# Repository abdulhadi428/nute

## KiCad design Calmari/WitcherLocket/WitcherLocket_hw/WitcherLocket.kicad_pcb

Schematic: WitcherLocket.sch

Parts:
C1, C3: 0.1u
C2, C4: 10u
D1: BAT54WS; SOD323
D2, D3, D4, D5, D6, D7, D8, D9: LED
DA1: NCP1400
HOLE1, HOLE2, HOLE3, HOLE4, HOLE5, HOLE6: HOLE_METALLED
L1: 22uH
R1, R3: 51R; RES_0603
R2, R4: 10R; RES_0603
SW1, SW2, SW3, SW4: SWITCH_2X
XL1, XL2: CONN_1

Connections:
+3.3V: C3.1, C4.1, D1.C, DA1.1 (CE), DA1.2 (OUT), SW1.2, SW2.2, SW3.2, SW4.2
+BATT: SW1.5, SW2.5, SW3.5, SW4.5, XL1.1
/Lout: D1.A, DA1.5 (LX), L1.1
/PWR_IN: C1.1, C2.1, L1.2, SW1.4, SW2.4, SW3.4, SW4.4
GND: C1.2, C2.2, C3.2, C4.2, D2.C, D3.C, D4.C, D5.C, D6.C, D7.C, D8.C, D9.C, DA1.4 (GND), XL2.1
unnamed: R2.1, SW2.3
unnamed: R3.1, SW3.3
unnamed: R4.1, SW4.3
unnamed: R1.1, SW1.3
unnamed: D4.A, D8.A, R3.2
unnamed: D5.A, D9.A, R4.2
unnamed: D2.A, D6.A, R1.2
unnamed: D3.A, D7.A, R2.2

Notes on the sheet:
-BATTERY
+BATTERY

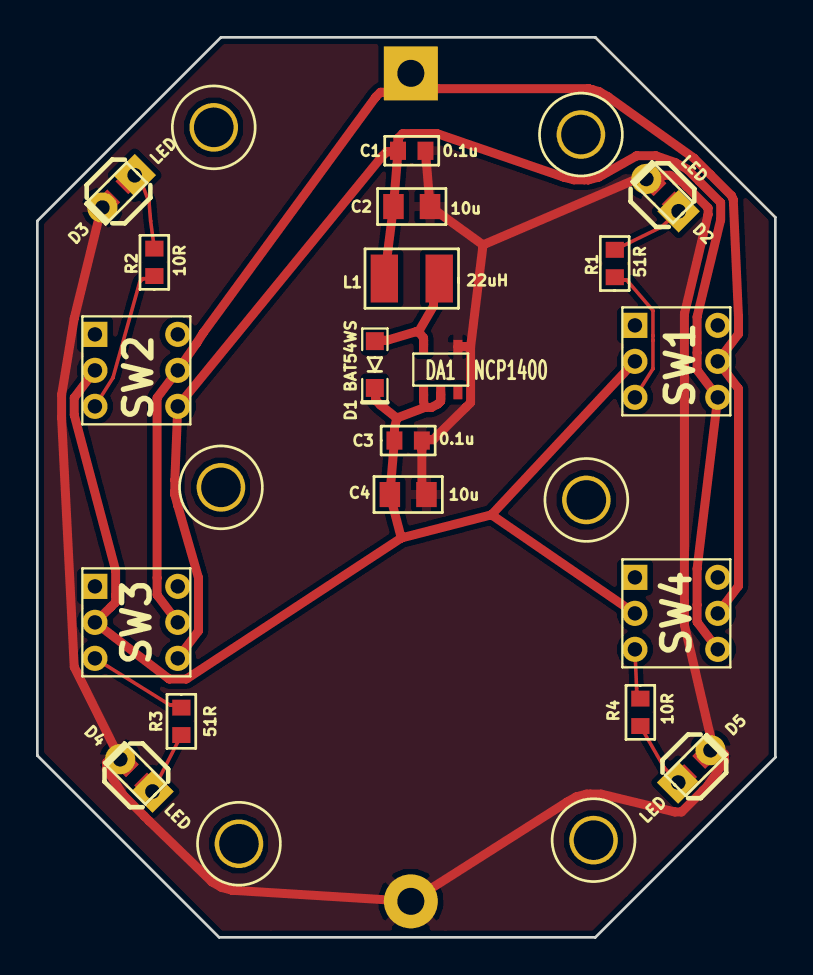
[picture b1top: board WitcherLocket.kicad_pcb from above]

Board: 2 copper layers, 41.0 x 50.0 mm, 31 parts (0 on the bottom side), 13 nets.

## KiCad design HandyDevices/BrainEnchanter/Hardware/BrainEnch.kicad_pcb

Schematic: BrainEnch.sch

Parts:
B1: BAT
BZ1: BUZZER
C1, C10: 10u; CAP_0805
C2, C3, C4: 0.1u; CAP_0402
C5: 10n; CAP_0402
C6: 1u; CAP_0402
C7, C12: 0.1u
C8, C13: 10u
C9, C11: 6.8pF
C14: 10uF; CAP_0603
C15: 1uF; CAP_0603
C16: 100uF 16V
C17: 0.1u; CAP_0603
D1, D2: BAT54WS
DA1: NCP1400
DA2: LM2703
DA4: MAX4453
DD1: STM32L151CXTX
HOLE1, HOLE2: HOLE_METALLED
L1: 22uH
L2, L3: 10uH; IND_0805
Q1: MMBT2222
Q2: NPN
R1: 1k
R2: 200k*; RES_0402
R3: 1k; RES_0402
R4: 51R; RES_0603
R5: 81k; RES_0603
R6: 10k; RES_0603
R7: 6.5k; RES_0603
R8: 20k; RES_0603
R9, R10: 1k; RES_0603
R11: 100R; RES_0603
R12: 100R; RES_0805
RP1, RP2: REFPOINT
SW1, SW2, SW3, SW4, SW5: BUTTON
TP1, TP2, TP3: TESTPOINT
XL1: CONN_3
XL2: ST_SWD
XL3: CONN_NOKIA_LCD10
XL4: CONN_2
XTAL1: 32768; CRYSTAL

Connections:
+3.3V: BZ1.1, C1.1, C2.1, C3.1, C4.1, C10.1, C12.1, C13.1, C14.1, C17.1, D1.C, DA1.1 (CE), DA1.2 (OUT), DA2.5 (VIN), DA4.8, DD1.1, DD1.24, DD1.36, DD1.48, L2.2, L3.2, XL2.1 (Vdd), XL3.9 (VDD), XL3.10 (VDDI)
+12V: C15.1, C16.1, D2.C, R5.1, R11.1
+BATT: B1.A, C7.1, C8.1, L1.2, R3.2
/12V_EN: DA2.4 (~SHDN), DD1.38
/ADC: DA4.7, DD1.12, R7.1, TP3.1
/BRAIN_A: R11.2, XL4.1
/BRAIN_C: Q2.3 (C), XL4.2 (PM)
/BTN1: DD1.40, SW1.1
/BTN2: DD1.41, SW2.1
/BTN3: DD1.42, SW3.1
/BTN4: DD1.43, SW4.1
/BTN5: DD1.45, SW5.1
/Buzzer: DD1.39, R1.1
/BuzzerOut: BZ1.2, Q1.3 (C)
/CURR_SNS: DA4.2, DA4.5, Q2.2 (E), R12.1
/DAC: DD1.14, R8.1, TP1.1
/LCD_BCKLT: DD1.27, R4.2
/LCD_SCLK: DD1.25, XL3.1 (CLK)
/LCD_SDA: DD1.21, XL3.2 (DATA)
/LCD_XCS: DD1.26, XL3.4 (CS)
/LCD_XRES: DD1.22, XL3.5 (RST)
/Lout: D1.A, DA1.5 (LX), L1.1
/Lout12: D2.A, DA2.1 (SW), L2.1
/SWCLK: DD1.37, XL2.2 (SWCLK)
/SWDIO: DD1.34, XL2.4 (SWDIO)
/UART_RX: DD1.31, XL1.3
/UART_TX: DD1.30, XL1.2 (PM)
GND: B1.C, C1.2, C2.2, C3.2, C4.2, C5.2, C6.2, C7.2, C8.2, C9.2, C10.2, C11.2, C12.2, C13.2, C14.2, C15.2, C16.2, C17.2, DA1.4 (GND), DA2.2 (GND), DA4.4, DD1.8, DD1.23, DD1.35, DD1.44, DD1.47, HOLE1.Hle, HOLE2.Hle, Q1.2 (E), R6.2, R9.2, R10.2, R12.2, SW1.2, SW2.2, SW3.2, SW4.2, SW5.2, XL1.1, XL2.3 (GND), XL3.3 (GND), XL3.7 (LED-)
unnamed: C5.1, C6.1, DD1.9, L3.1
unnamed: Q1.1 (B), R1.2
unnamed: R4.1, XL3.6 (LED+)
unnamed: DD1.10, R3.1
unnamed: DA4.6, R7.2, R10.1
unnamed: C9.1, R2.2, XTAL1.1
unnamed: C11.1, DD1.3, XTAL1.2
unnamed: DA2.3 (FB), R5.2, R6.1
unnamed: DD1.4, R2.1
unnamed: DA4.3, R8.2, R9.1
unnamed: DA4.1, Q2.1 (B), TP2.1

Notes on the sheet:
Debug port
Programming
CPU
Power
1xAAA
LCD
Stabilizer

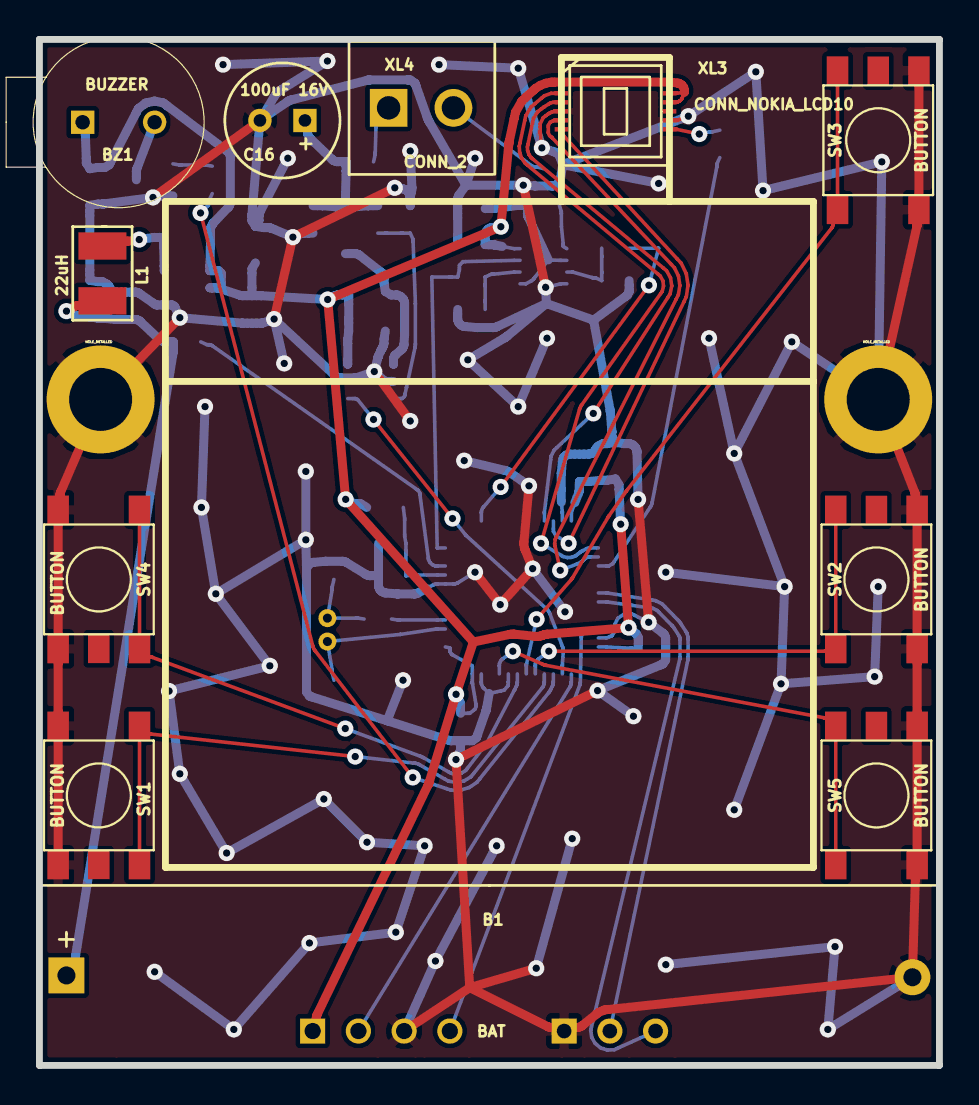
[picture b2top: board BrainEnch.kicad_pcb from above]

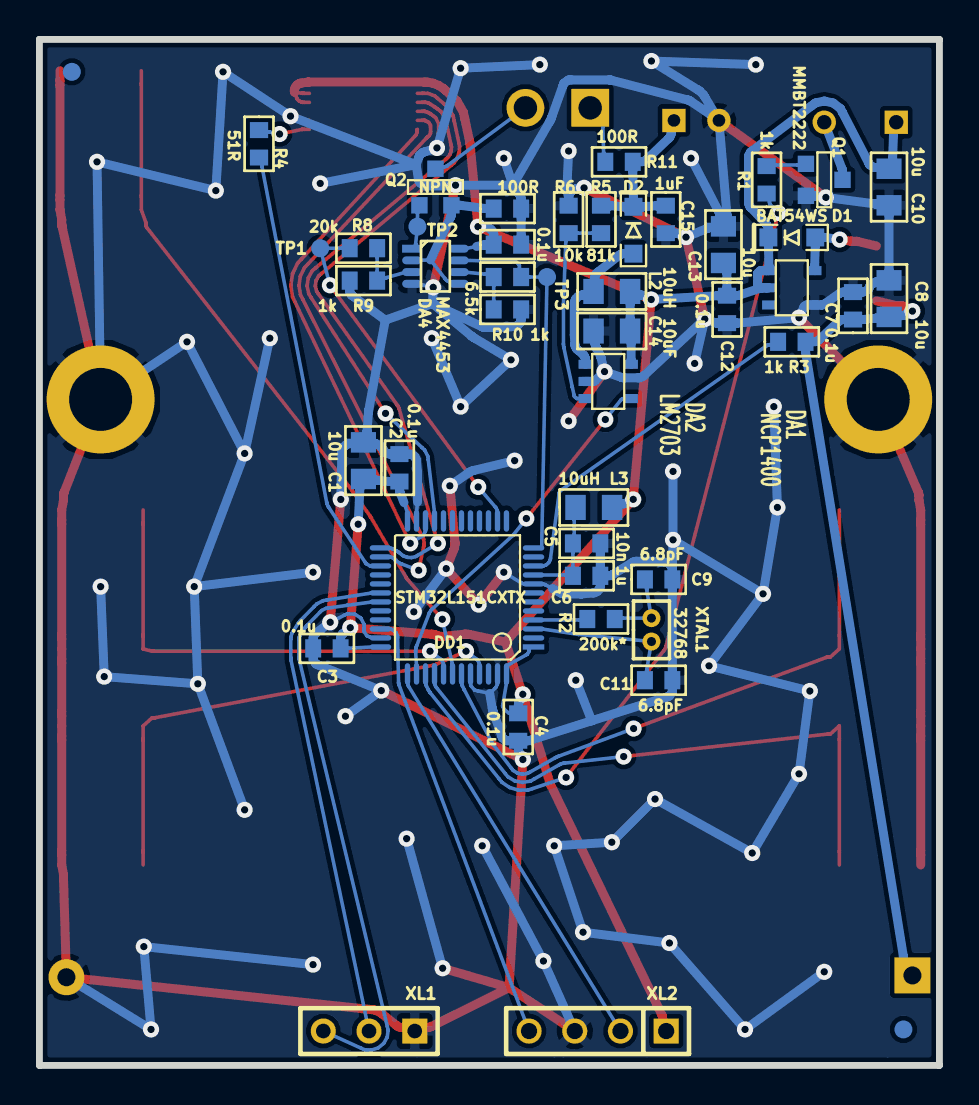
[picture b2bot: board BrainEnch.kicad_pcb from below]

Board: 2 copper layers, 50.0 x 57.0 mm, 59 parts (46 on the bottom side), 39 nets.

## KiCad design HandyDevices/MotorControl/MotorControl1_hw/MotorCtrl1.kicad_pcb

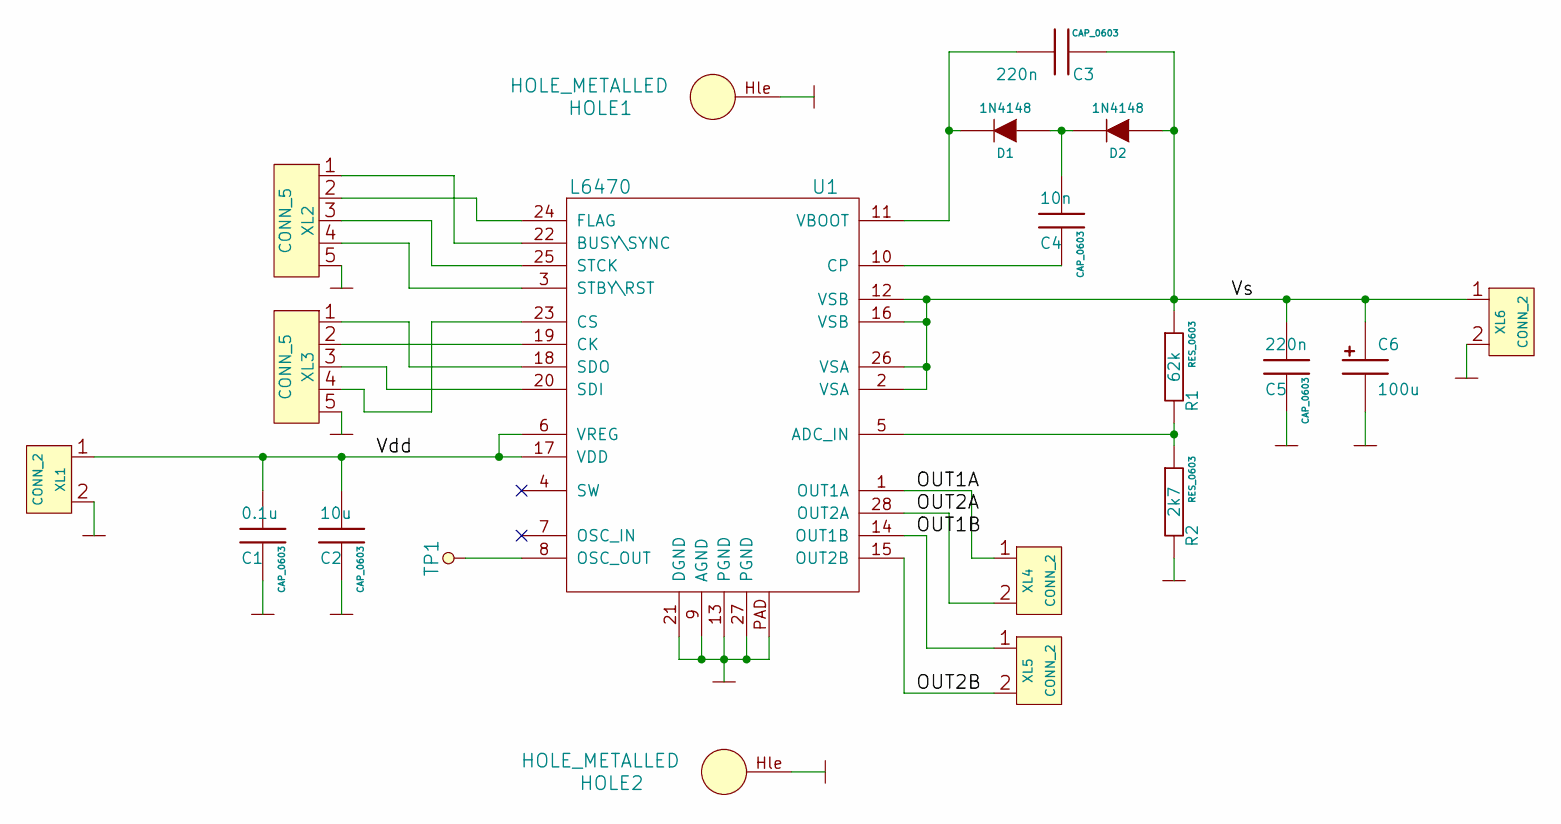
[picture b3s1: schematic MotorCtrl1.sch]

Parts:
C1: 0.1u; CAP_0603
C2: 10u; CAP_0603
C3, C5: 220n; CAP_0603
C4: 10n; CAP_0603
C6: 100u
D1, D2: 1N4148
HOLE1, HOLE2: HOLE_METALLED
R1: 62k; RES_0603
R2: 2k7; RES_0603
TP1: TESTPOINT
U1: L6470
XL1, XL4, XL5, XL6: CONN_2
XL2, XL3: CONN_5

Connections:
/OUT1A: U1.1 (OUT1A), XL4.1
/OUT1B: U1.14 (OUT1B), XL5.1
/OUT2A: U1.28 (OUT2A), XL4.2 (PM)
/OUT2B: U1.15 (OUT2B), XL5.2 (PM)
/Vdd: C1.1, C2.1, U1.6 (VREG), U1.17 (VDD), XL1.1
/Vs: C3.2, C5.1, C6.1, D2.A, R1.1, U1.2 (VSA), U1.12 (VSB), U1.16 (VSB), U1.26 (VSA), XL6.1
GND: C1.2, C2.2, C5.2, C6.2, HOLE1.Hle, HOLE2.Hle, R2.2, U1.9 (AGND), U1.13 (PGND), U1.21 (DGND), U1.27 (PGND), U1.PAD, XL1.2 (PM), XL2.5, XL3.5, XL6.2 (PM)
unnamed: C4.2, U1.10 (CP)
unnamed: C4.1, D1.A, D2.C
unnamed: C3.1, D1.C, U1.11 (VBOOT)
unnamed: R1.2, R2.1, U1.5 (ADC_IN)
unnamed: U1.18 (SDO), XL3.1
unnamed: U1.19 (CK), XL3.2
unnamed: U1.20 (SDI), XL3.3
unnamed: U1.3 (STBY\RST), XL2.4
unnamed: TP1.1, U1.8 (OSC_OUT)
unnamed: U1.22 (BUSY\SYNC), XL2.1
unnamed: U1.23 (CS), XL3.4
unnamed: U1.24 (FLAG), XL2.2
unnamed: U1.25 (STCK), XL2.3

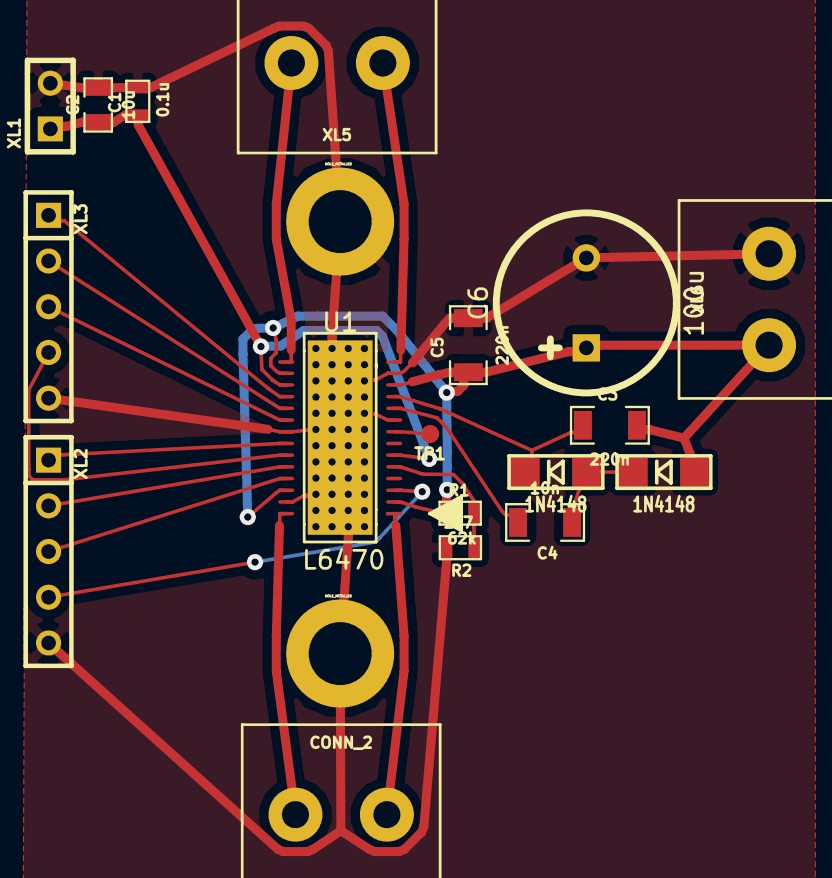
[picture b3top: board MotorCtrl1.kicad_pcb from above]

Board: 2 copper layers, 20 parts (0 on the bottom side), 20 nets.

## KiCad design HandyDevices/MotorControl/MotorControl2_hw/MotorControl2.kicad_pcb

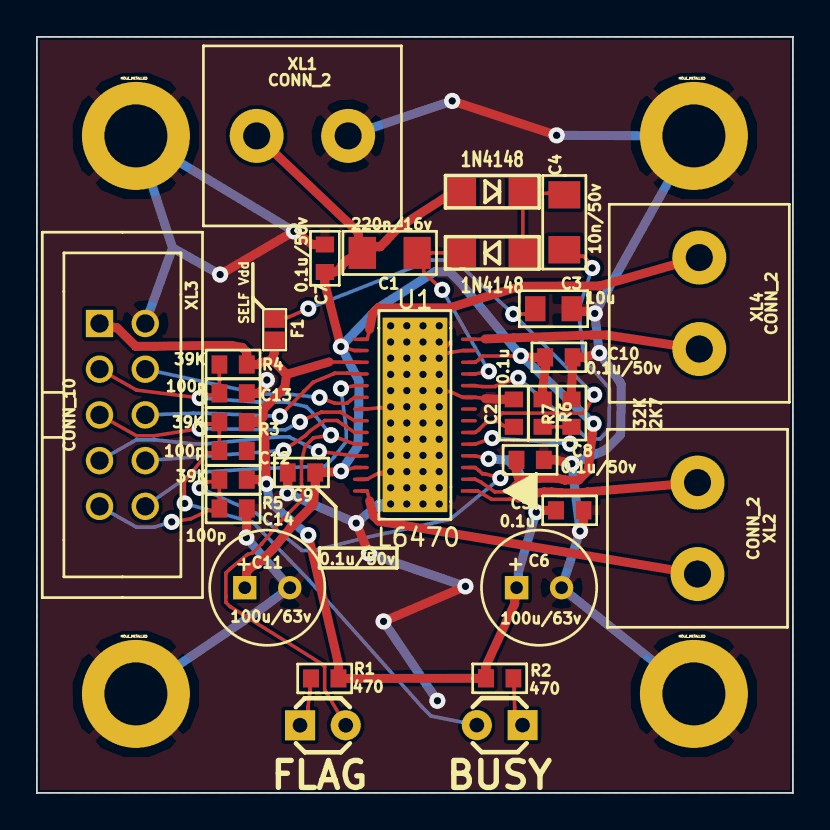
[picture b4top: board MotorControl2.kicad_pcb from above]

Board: 2 copper layers, 42.0 x 42.0 mm, 35 parts (0 on the bottom side), 22 nets.

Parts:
C1: 220n/16v; CAP_1206
C2, C5: 0.1u; CAP_0603
C3: 10u; CAP_0805
C4: 10n/50v; CAP_1206
C6, C11: 100u/63v; CAP_06xxR
C7, C8, C9, C10: 0.1u/50v; CAP_0603
C12, C13, C14: 100p; CAP_0603
D1, D2: LED; LED-3MM
D3, D4: 1N4148; DIODE_SOD80C
F1: FUSE0R; SMD0603_FUSE
HOLE1, HOLE2, HOLE3, HOLE4: HOLE_METALLED; Hole3_5_out6mm
R1, R2: 470; RES_0603
R3, R4, R5: 39K; RES_0603
R6: 32K; RES_0603
R7: 2K7; RES_0603
U1: L6470; HTSSOP28
XL1, XL2, XL4: CONN_2; CONN_KF128D_2
XL3: CONN_10; CONN_IDC_2X5

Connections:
/ADC_IN: R6.2, R7.1, U1.5
/BUSY/SYNC: C12.1, D2.C, R3.2, U1.22, XL3.5
/CK: U1.19, XL3.10
/CS: U1.23, XL3.8
/EXT_VDD: C5.1, C6.1, F1.2, R1.1, R2.1, R3.1, R4.1, R5.1, U1.4, U1.17, XL3.1
/FLAG: C13.1, D1.C, R4.2, U1.24, XL3.3
/MISO: U1.18, XL3.6
/MOSI: U1.20, XL3.4
/Mtr1A: U1.1, XL2.1
/Mtr1B: U1.14, XL4.1
/Mtr2A: U1.28, XL2.2
/Mtr2B: U1.15, XL4.2
/STBY/RST: C14.1, R5.2, U1.3, XL3.9
/STCK: U1.25, XL3.7
/Vs: C1.2, C7.1, C8.1, C9.1, C10.1, C11.1, D4.A, R6.1, U1.2, U1.12, U1.16, U1.26, XL1.1
GND: C2.2, C3.2, C5.2, C6.2, C7.2, C8.2, C9.2, C10.2, C11.2, C12.2, C13.2, C14.2, HOLE1.Hle, HOLE2.Hle, HOLE3.Hle, HOLE4.Hle, R7.2, U1.9, U1.13, U1.21, U1.27, U1.PAD, XL1.2, XL3.2
unnamed: C2.1, C3.1, F1.1, U1.6
unnamed: D2.A, R2.2
unnamed: D1.A, R1.2
unnamed: C4.1, D3.A, D4.C
unnamed: C4.2, U1.10
unnamed: C1.1, D3.C, U1.11

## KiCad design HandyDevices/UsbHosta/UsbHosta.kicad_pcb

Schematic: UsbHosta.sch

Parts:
C1, C2, C4, C5, C7, C8, C10, C11, C13, C14: 0.1u; CAP_0603
C3, C6, C9, C12, C15: 1000u
D1, D2, D3, D4, D5, D6: LED
DA1, DA2, DA3, DA4, DA5: TPS202X
HOLE1, HOLE2, HOLE3, HOLE4, HOLE5, HOLE6: HOLE_METALLED
R1, R2, R3, R4, R5, R6: 1k; RES_0603
XL1, XL2, XL3, XL4, XL5, XL6, XL7, XL8, XL9, XL10: CONN_1
XL11, XL12, XL13, XL14, XL15, XL16, XL17, XL18, XL19, XL20: USB_A_X2

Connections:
+5V: C1.1, C4.1, C7.1, C10.1, C13.1, DA1.2, DA1.3, DA2.2, DA2.3, DA3.2, DA3.3, DA4.2, DA4.3, DA5.2, DA5.3, HOLE2.Hle, HOLE4.Hle, HOLE6.Hle, R1.1, R2.1, R3.1, R4.1, R5.1, R6.1, XL1.1, XL2.1, XL3.1, XL4.1, XL5.1
/OUT1: C8.1, C9.1, DA3.6, DA3.7, DA3.8, XL15.1, XL15.5, XL16.1, XL16.5
/OUT2: C11.1, C12.1, DA4.6, DA4.7, DA4.8, XL17.1, XL17.5, XL18.1, XL18.5
/OUT3: C2.1, C3.1, DA1.6, DA1.7, DA1.8, XL11.1, XL11.5, XL12.1, XL12.5
/OUT4: C5.1, C6.1, DA2.6, DA2.7, DA2.8, XL13.1, XL13.5, XL14.1, XL14.5
/OUT5: C14.1, C15.1, DA5.6, DA5.7, DA5.8, XL19.1, XL19.5, XL20.1, XL20.5
GND: C1.2, C2.2, C3.2, C4.2, C5.2, C6.2, C7.2, C8.2, C9.2, C10.2, C11.2, C12.2, C13.2, C14.2, C15.2, D2.C, DA1.1, DA1.4, DA2.1, DA2.4, DA3.1, DA3.4, DA4.1, DA4.4, DA5.1, DA5.4, HOLE1.Hle, HOLE3.Hle, HOLE5.Hle, XL6.1, XL7.1, XL8.1, XL9.1, XL10.1, XL11.4, XL11.8, XL11.SHLD, XL12.4, XL12.8, XL12.SHLD, XL13.4, XL13.8, XL13.SHLD, XL14.4, XL14.8, XL14.SHLD, XL15.4, XL15.8, XL15.SHLD, XL16.4, XL16.8, XL16.SHLD, XL17.4, XL17.8, XL17.SHLD, XL18.4, XL18.8, XL18.SHLD, XL19.4, XL19.8, XL19.SHLD, XL20.4, XL20.8, XL20.SHLD
unnamed: XL14.2, XL14.3
unnamed: XL14.6, XL14.7
unnamed: XL13.2, XL13.3
unnamed: XL13.6, XL13.7
unnamed: D6.A, R6.2
unnamed: D6.C, DA5.5
unnamed: XL12.2, XL12.3
unnamed: XL12.6, XL12.7
unnamed: D3.C, DA2.5
unnamed: D3.A, R3.2
unnamed: XL19.2, XL19.3
unnamed: XL19.6, XL19.7
unnamed: XL20.2, XL20.3
unnamed: D2.A, R2.2
unnamed: XL20.6, XL20.7
unnamed: XL16.6, XL16.7
unnamed: XL16.2, XL16.3
unnamed: XL15.2, XL15.3
unnamed: XL15.6, XL15.7
unnamed: D5.C, DA4.5
unnamed: D5.A, R5.2
unnamed: D4.C, DA3.5
unnamed: D4.A, R4.2
unnamed: D1.C, DA1.5
unnamed: D1.A, R1.2
unnamed: XL11.2, XL11.3
unnamed: XL11.6, XL11.7
unnamed: XL17.6, XL17.7
unnamed: XL17.2, XL17.3
unnamed: XL18.6, XL18.7
unnamed: XL18.2, XL18.3

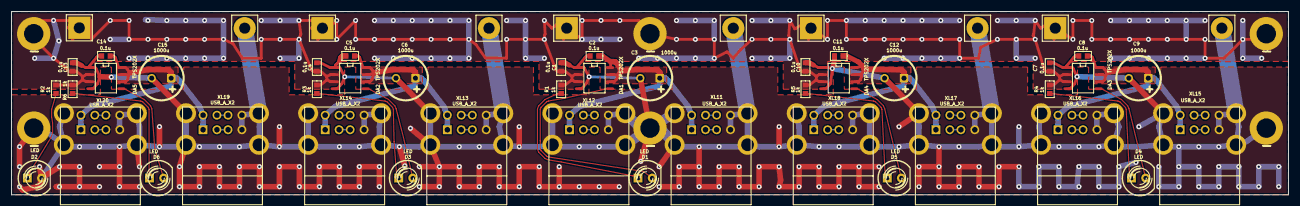
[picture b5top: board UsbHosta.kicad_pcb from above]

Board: 2 copper layers, 230.0 x 33.0 mm, 58 parts (0 on the bottom side), 38 nets.

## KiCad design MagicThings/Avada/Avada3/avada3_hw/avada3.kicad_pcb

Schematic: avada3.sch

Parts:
B1, B2, B3: BAT
BZ1: BUZZER
C1, C2, C3, C6, C9: 0.1u
C4: 4.7u
C5, C11, C14: 0.1u; CAP_0603
C7: 1u
C8, C10: 10u
C12: 10uF; CAP_0603
C13: 1000u
C15: 10u; CAP_0603
D1: LED_RAD
DA1: NCP583SQ
DA2: MAX4453
DD1: STM32F100C4
F1: FUSE0R
HOLE1, HOLE2, HOLE3: HOLE_METALLED
Q1: IRLMS6702
Q2: IRLMS1503
Q3: N_Ch_SOT23
Q4: IRLML9303
Q5: MMBT2222
R1, R2: 4K7; RES_0402
R3: 150; RES_0402
R4, R5: 390k
R6: 20k; RES_0603
R7, R8: 1k; RES_0603
R9: 1k
R10: 0.1R; RES_0805
SW1: SWITCH_H
SW2: BUTTON_H
XL1: CONN_3
XL2: ST_SWD
XL3: CONN_4

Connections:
+3.3V: BZ1.1, C1.1, C2.1, C3.1, C4.1, C5.2, C7.1, C9.1, C10.1, C11.1, C15.1, DA1.3 (Vout), DA2.8, DD1.1 (VBAT), DD1.9 (VDDA), DD1.24 (VDD1), DD1.36 (VDD2), DD1.48 (VDD3), XL2.1 (Vdd)
+BATT: C6.1, C8.1, C13.1, C14.1, DA1.1 (EN), DA1.4 (Vin), F1.1, Q1.4 (Src), Q4.2 (S), R4.1, R8.1, SW1.1
/BAT_IN: B3.A, SW1.2
/Buzzer: DD1.29 (T1C1/CK1/PA8), R9.1
/BuzzerOut: BZ1.2, Q5.3 (C)
/CURR_SNS: DA2.2, Q2.4 (Src), Q3.2 (S), R10.1
/DAC: C12.1, DD1.14 (ADC1-4/DAC1/CK2/PA4)
/GreenEn: DD1.13 (ADC1-3/T2C4/T15C2/RX2/PA3), Q1.3 (Gate), Q4.1 (G), R8.2
/LED_A: D1.A, F1.2, Q1.1 (Drain), Q1.2 (Drain), Q1.5 (Drain), Q1.6 (Drain), Q4.3 (D)
/LED_C: D1.C, Q2.1 (Drain), Q2.2 (Drain), Q2.5 (Drain), Q2.6 (Drain), Q3.3 (D)
/P_SCL: DD1.42 (PB6/SCL1/T16C1N), R1.1, XL3.2 (PM)
/P_SDA: DD1.43 (PB7/SDA1/T17C1N), R2.1, XL3.4
/PeriphPwr: DD1.41 (PB5/(T3C2)), R1.2, R2.2, R3.2
/PeriphPwr1: R3.1, XL3.1
/SWCLK: DD1.37 (SWCLK/(JTCK)/(PA14)), XL2.2 (SWCLK)
/SWDIO: DD1.34 (SWDIO/(JTMS)/(PA13)), XL2.4 (SWDIO)
/UART_RX: DD1.31 (T1C3/RX1/PA10), XL1.3
/UART_TX: DD1.30 (T1C2/TX1/PA9), XL1.2 (PM)
/UBat/2: DD1.18 (PB0/T3C3/ADC1-8), R4.2, R5.1
GND: B1.C, C1.2, C2.2, C3.2, C4.2, C5.1, C6.2, C7.2, C8.2, C9.2, C10.2, C11.2, C13.2, C14.2, C15.2, DA1.2 (GND), DA2.4, DD1.8 (VSSA), DD1.23 (VSS1), DD1.35 (VSS2), DD1.44 (BOOT0), DD1.47 (VSS3), HOLE1.Hle, HOLE2.Hle, HOLE3.Hle, Q5.2 (E), R5.2, R7.2, R10.2, SW1.H, SW2.2, SW2.H, XL1.1, XL2.3 (GND), XL3.3
unnamed: B1.A, B2.C
unnamed: Q5.1 (B), R9.2
unnamed: C12.2, R6.1
unnamed: DD1.10 (ADC1-0/WKUP/PA0), SW2.1
unnamed: B2.A, B3.C
unnamed: DA2.1, Q2.3 (Gate), Q3.1 (G)
unnamed: DA2.3, R6.2, R7.1

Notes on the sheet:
Programming
Battery meter
Stabilizer
Debug port
Peripheral I2C Pull-Ups
Pill Connector
Pill
Choose one of two packages
Place R and use OpenDrain output if transistor does not close properly

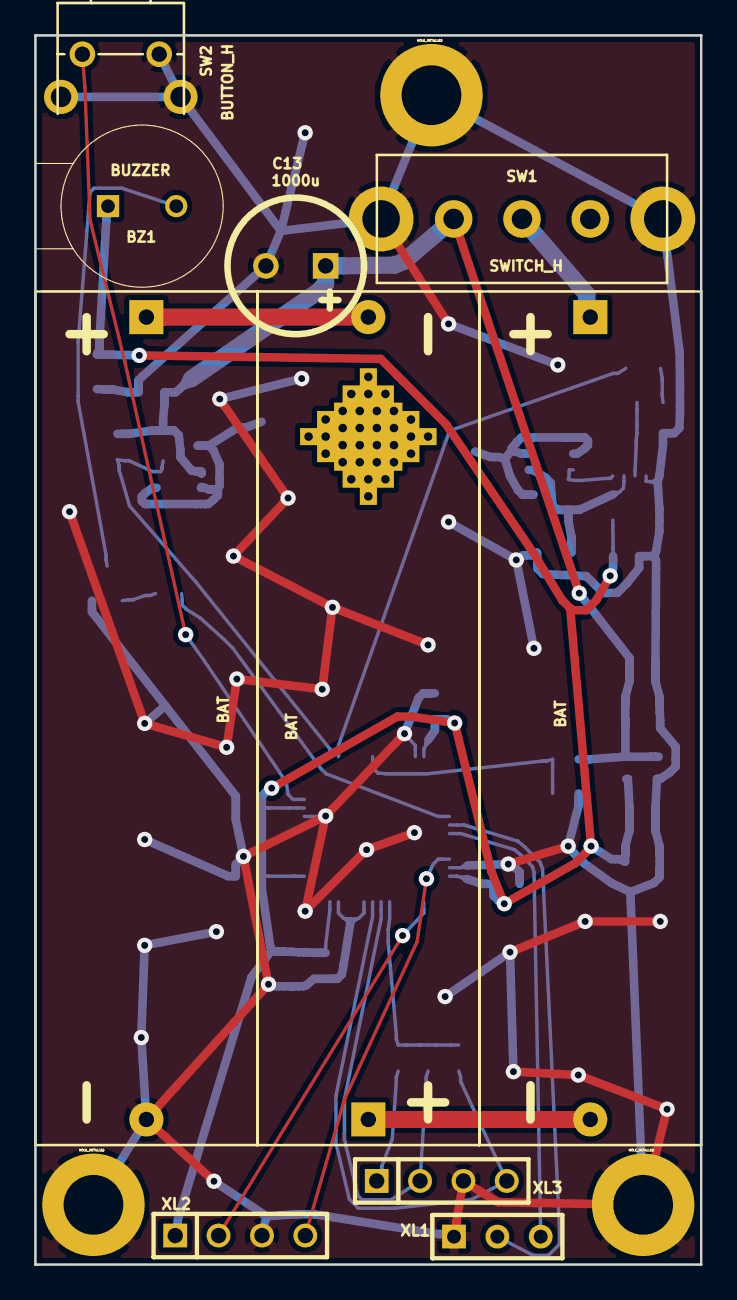
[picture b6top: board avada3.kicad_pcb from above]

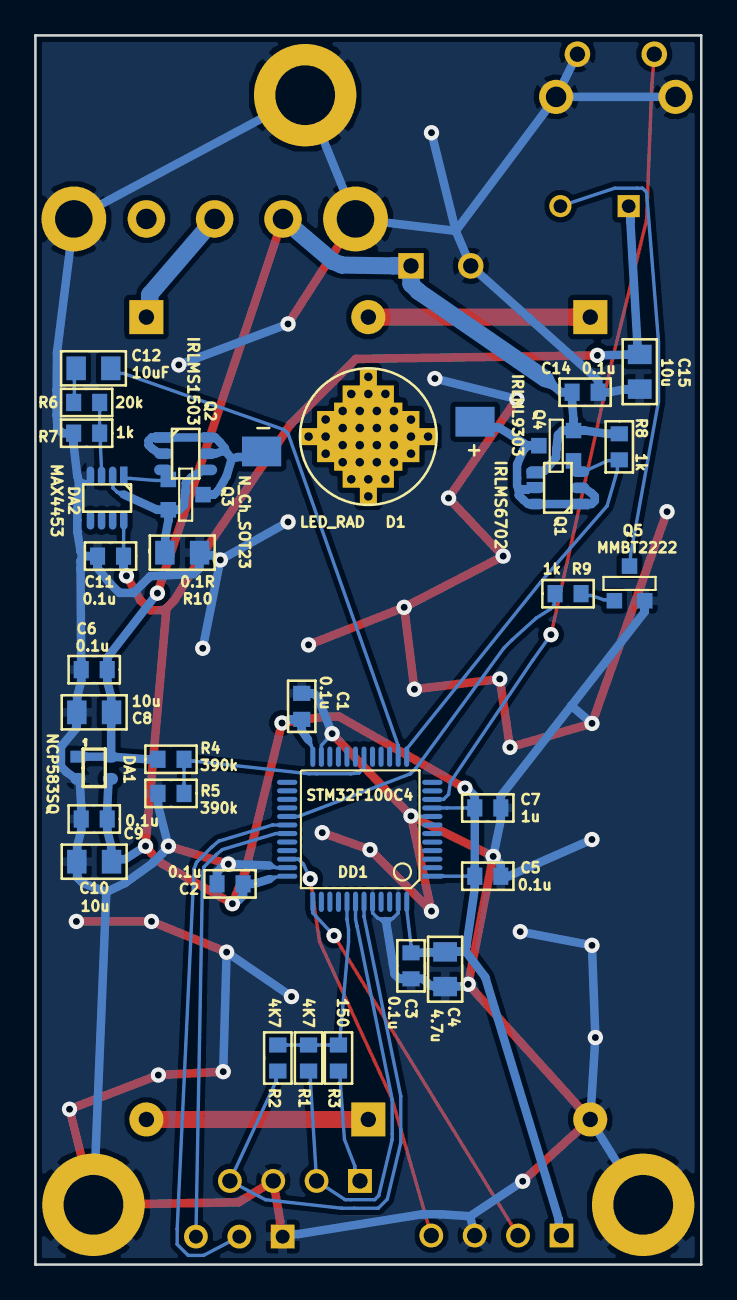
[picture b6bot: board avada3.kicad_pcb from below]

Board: 2 copper layers, 39.0 x 72.0 mm, 47 parts (34 on the bottom side), 27 nets.

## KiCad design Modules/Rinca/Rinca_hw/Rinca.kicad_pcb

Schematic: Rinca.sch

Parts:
ANT1: ANT_PCB_NOCNTR
B1: BAT
C1, C3, C5, C7, C8, C9, C11, C12, C18, C19, C22, C24, C25, C27: 0.1u
C2, C4, C6, C14, C17: 10u
C10: 1000u
C13, C16: 1u
C15: 1000pF
C20, C21: 10pF; CAP_0402
C23, C26, C28: 220pF
D1: D_SHOTTKY
D2: LED
DA1: IPS6041
DA2: NCP1400
DA3: TPS71533
DA4: LP2951
DD1: STM32F10X-48
DD2: MMA8452Q
DD3: CC2500
F1, F2, F3, F4: FUSE0R
HOLE1, HOLE2: HOLE_METALLED
L1: 22uH
R1: 10k
R2: 51R; RES_0603
R3: 200k
R4: 120k
R5: 1k
R6: 100R
R7: 56k
R8, R9: 4k7
RP1, RP2: REFPOINT
SW1: SWITCH
SW2, SW3, SW4: BUTTON
TP1: TESTPOINT
XL1: CONN_1
XL2: RJ11
XL3: ST_SWD
XL5: BARREL_SOCKET
XL6: CONN_3
XTAL1: 27MHz; 03225

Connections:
+3.3V: C5.1, C6.1, C7.1, C8.1, C9.1, C11.1, C13.1, C15.1, C16.1, C17.1, C18.1, C23.1, C24.1, C25.1, C26.1, C27.1, C28.1, D1.C, DA2.1 (CE), DA2.2 (OUT), DA3.5 (OUT), DA4.1 (Out), DD1.1 (VBAT), DD1.9 (VDDA), DD1.24 (VDD1), DD1.36 (VDD2), DD1.48 (VDD3), DD2.1 (VDDIO), DD2.14 (VDD), DD3.4 (DVDD), DD3.9 (AVDD), DD3.11 (AVDD), DD3.14 (AVDD), DD3.15 (AVDD), DD3.18 (DGUARD), R3.1, R8.1, R9.2, XL3.1 (Vdd); also elsewhere on the board
+BATT: C1.1, C2.1, C3.1, C4.1, C10.1, C12.1, C14.1, DA1.5 (Vcc), DA1.6 (Vcc), DA1.7 (Vcc), DA1.8 (Vcc), DA3.4 (IN), DA4.8 (In), L1.2, R5.1, SW1.1, XL2.3
/ACC_INT1: DD1.41 (PB5/(T3C2)), DD2.11 (INT1)
/ADC_BAT: DD1.10 (ADC1-0/WKUP/PA0), R5.2
/Ant1: ANT1.1, DD3.12 (RF_P)
/Ant2: ANT1.2, DD3.13 (RF_N)
/BUTTON1: DD1.32 (T1C4/USBDM/PA11), SW2.1
/BUTTON2: DD1.33 (USBDP/PA12), SW3.1
/BUTTON3: DD1.38 (JTDI/PA15), SW4.1
/CC_CS: DD1.14 (ADC1-4/DAC1/CK2/PA4), DD3.7 (CSn)
/CC_GDO0: DD1.13 (ADC1-3/T2C4/T15C2/RX2/PA3), DD3.6 (GDO0), TP1.1
/CC_MISO: DD1.16 (ADC1-6/T3C1/MISO1/PA6), DD3.2 (SO(GDO1))
/CC_MOSI: DD1.17 (ADC1-7/T3C2/MOSI1/PA7), DD3.20 (SI)
/CC_SCK: DD1.15 (ADC1-5/DAC2/SCK1/PA5), DD3.1 (SCLK)
/Ch1_ERROR: DA1.3 (Diag), DD1.39 (PB3/JTDO/(T2C2))
/Ch1_IN: DD1.40 (PB4/JTRST/(T3C1)), R1.1
/Ch1_OUT: DA1.4 (Out), XL5.PWR
/GPIO0: DD1.18 (PB0/T3C3/ADC1-8), F1.2
/GPIO1: DD1.19 (PB1/T3C4/ADC1-9), F2.2
/GPIO2: DD1.45 (PB8/T4C3/T16C1), F3.2
/GPIO3: DD1.46 (PB9/T4C4/T17C1), F4.2
/I2C_SCL: DD1.42 (PB6/SCL1/T4C1/T16C1N), DD2.4 (SCL), R8.2
/I2C_SDA: DD1.43 (PB7/SDA1/T4C2/T17C1N), DD2.6 (SDA), R9.1
/LCD_BCKLT: DD1.28 (PB15/MOSI2/T1C3N/(T15C2)), R2.2
/LCD_SCLK: DD1.25 (PB12/CK3); also elsewhere on the board
/LCD_SDA: DD1.21 (PB10/SCL2/TX3); also elsewhere on the board
/LCD_XCS: DD1.27 (PB14/MISO2/T1C2N/(T15C1)); also elsewhere on the board
/LCD_XRES: DD1.22 (PB11/SDA2/RX3); also elsewhere on the board
/Lout: D1.A, DA2.5 (LX), L1.1
/RX1: DD1.31 (T1C3/RX1/PA10), XL6.1
/SWCLK: DD1.37 (SWCLK/JTCK/PA14), XL3.2 (SWCLK)
/SWDIO: DD1.34 (SWDIO/JTMS/PA13), XL3.4 (SWDIO)
/TX1: DD1.30 (T1C2/TX1/PA9), XL6.2 (PM)
GND: B1.C, C1.2, C2.2, C3.2, C4.2, C5.2, C6.2, C7.2, C8.2, C9.2, C10.2, C11.2, C12.2, C13.2, C14.2, C16.2, C17.2, C18.2, C19.2, C20.2, C21.2, C22.2, C23.2, C24.2, C25.2, C26.2, C27.2, C28.2, D2.C, DA1.1 (GND), DA2.4 (GND), DA3.2 (GND), DA4.3 (Shdn), DA4.4 (GND), DD1.8 (VSSA), DD1.23 (VSS1), DD1.35 (VSS2), DD1.44 (BOOT0), DD1.47 (VSS3), DD2.5 (GND), DD2.7 (SA0), DD2.10 (GND), DD2.12 (GND), DD3.16 (GND), DD3.19 (GND), DD3.PAD (GND), HOLE1.Hle, HOLE2.Hle, R4.2, R7.2, SW2.2, SW3.2, SW4.2, XL1.1, XL2.4, XL2.H (GND), XL3.3 (GND), XL5.GND, XL6.3, XTAL1.H; also elsewhere on the board
unnamed: D2.A, R6.1
unnamed: C19.1, DD2.2 (BYP)
unnamed: DD3.17 (RBIAS), R7.1
unnamed: C22.1, DD3.5 (DCOUPL)
unnamed: F2.1, XL2.2
unnamed: F4.1, XL2.6
unnamed: B1.A, SW1.2
unnamed: DA1.2 (Input), R1.2
unnamed: F3.1, XL2.5
unnamed: F1.1, XL2.1
unnamed 44: R2.1; also elsewhere on the board
unnamed: C15.2, DA4.7 (Feedback), R3.2, R4.1
unnamed: DD1.11 (ADC1-1/T2C2/PA1), R6.2
unnamed: C21.1, DD3.10 (XOSC_Q2), XTAL1.2
unnamed: C20.1, DD3.8 (XOSC_Q1), XTAL1.1

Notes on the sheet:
Accelerometer I2C addr = 0x1C
Programming
LCD
Different packages
3.3V power regulator (Choose one or another)

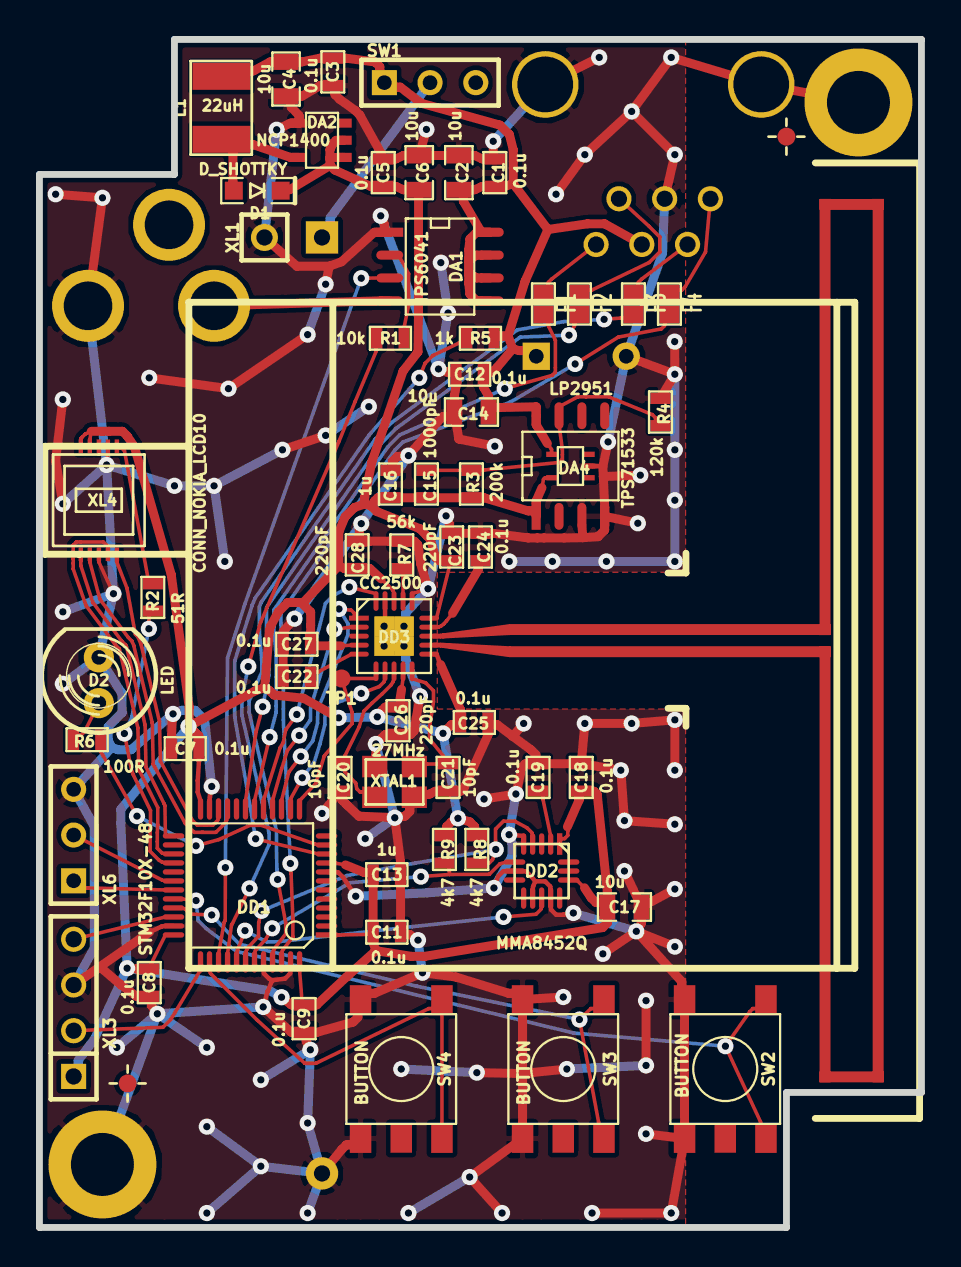
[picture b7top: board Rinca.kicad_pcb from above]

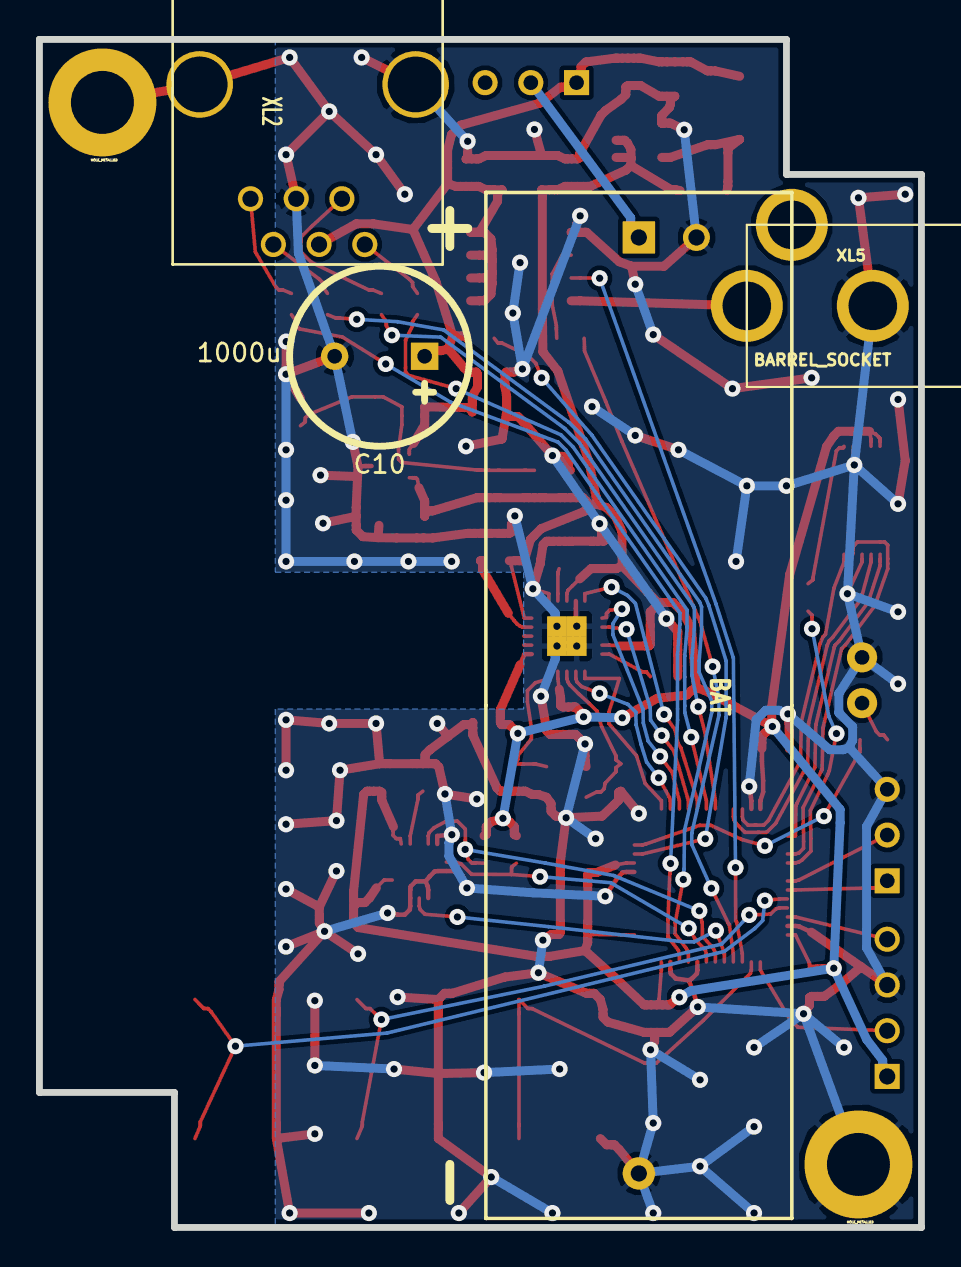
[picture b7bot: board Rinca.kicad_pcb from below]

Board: 2 copper layers, 49.0 x 66.0 mm, 69 parts (6 on the bottom side), 49 nets.

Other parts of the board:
XL4: CONN_NOKIA_LCD10; CONN_NOKIA1101_LCD

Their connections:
+3.3V: XL4.9, XL4.10; also elsewhere on the board
/LCD_SCLK: XL4.1; also elsewhere on the board
/LCD_SDA: XL4.2; also elsewhere on the board
/LCD_XCS: XL4.4; also elsewhere on the board
/LCD_XRES: XL4.5; also elsewhere on the board
GND: XL4.3, XL4.7; also elsewhere on the board
unnamed 44: XL4.6; also elsewhere on the board

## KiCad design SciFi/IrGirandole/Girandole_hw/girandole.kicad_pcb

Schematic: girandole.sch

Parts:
BZ1: BUZZER
C1: 3.3pF; CAP_0603
C2: 0.1u
C3: 1000u
C5, C11: 0.1u; CAP_0603
C6, C10: 1n; CAP_0603
C7, C9: 1u; CAP_0603
C8, C41: 10u; CAP_0805
C15, C18: 20pF; CAP_0402
C38, C39, C40, C43, C44: 0.1u; CAP_0402
D1: LED
D2, D3, D4, D5: LED
DA1: MAX4453
DA2: LP2951
DD2: STM32F10X-48
F1, F2, F3, F4, F5, F6, F7, F8: FUSE0R
HOLE1, HOLE2, HOLE3, HOLE4: HOLE_METALLED
Q1: TSOP752XX
Q2: LED_RGB 5050
Q3: TSOP48XX
Q4, Q6: MMBT2222
Q5: BD139-16
R1, R4, R6: 51R; RES_0603
R2, R9, R10: 1k; RES_0603
R3: 220R; RES_0402
R5: 30k; RES_0603
R7: 100
R8, R14: 20R; RES_0603
R11: 0.1R; RES_0805
R12: 20k; RES_0603
R13: 12k; RES_0603
TP1, TP2: TESTPOINT
XL1: CONN_2
XL5: CONN_3
XL6: ST_SWD
XL7: CONN_1
XTAL2: 12.0MHz; 0532

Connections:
+3.3V: C6.1, C7.1, C8.1, C11.1, C38.1, C39.1, C40.1, C41.1, C43.1, C44.1, DA1.8, DA2.1 (Out), DD2.1 (VBAT), DD2.9 (VDDA), DD2.24 (VDD1), DD2.36 (VDD2), DD2.48 (VDD3), R12.1, XL6.1 (Vdd)
+BATT: BZ1.1, C3.1, C5.1, C9.1, C10.1, D2.A, DA2.8 (In), F8.1, XL1.1
/Buzzer: DD2.27 (PB14/MISO2/T1C2N/(T15C1)), R2.1
/BuzzerOut: BZ1.2, Q4.3 (C)
/CURR_SNS: DA1.2, Q5.3 (E), R11.1
/DAC: DD2.14 (ADC1-4/DAC1/CK2/PA4), R5.1, TP1.1
/Debug: DD2.18 (PB0/T3C3/ADC1-8), XL7.1
/LED1_OUT: C1.2, D5.C, Q5.2 (C)
/LED2_OUT: D4.C, D5.A, R14.2
/LED3_OUT: D3.C, D4.A, F8.2
/LED4_OUT: D2.C, D3.A, R8.2
/RX1: DD2.31 (T1C3/RX1/PA10), XL5.3
/SWCLK: DD2.37 (SWCLK/JTCK/PA14), XL6.2 (SWCLK)
/SWDIO: DD2.34 (SWDIO/JTMS/PA13), XL6.4 (SWDIO)
/TIM: DD2.29 (T1C1/CK1/PA8), R9.1
/TX1: DD2.30 (T1C2/TX1/PA9), XL5.2 (PM)
/XotarIn: DD2.10 (ADC1-0/WKUP/PA0), DD2.16 (ADC1-6/T3C1/MISO1/PA6), Q1.3 (OUT), Q3.1
/XotarPower: DD2.17 (ADC1-7/T3C2/MOSI1/PA7), R7.1
GND: C2.2, C3.2, C5.2, C7.2, C8.2, C9.2, C10.2, C11.2, C15.2, C18.2, C38.2, C39.2, C40.2, C41.2, C43.2, C44.2, D1.C, DA1.4, DA2.3 (Shdn), DA2.4 (GND), DD2.8 (VSSA), DD2.23 (VSS1), DD2.35 (VSS2), DD2.44 (BOOT0), DD2.47 (VSS3), F1.2, F2.2, F3.2, F4.2, F5.2, F6.2, F7.2, HOLE1.Hle, HOLE2.Hle, HOLE3.Hle, HOLE4.Hle, Q1.1 (GND), Q1.4 (GND), Q2.BC (B), Q2.GC (G), Q2.RC, Q3.2, Q4.2 (E), Q6.2 (E), R10.2, R11.2, R13.2, XL1.2 (PM), XL5.1, XL6.3 (GND), XTAL2.H
unnamed: DD2.6 (OSCOUT/(PD1)), R3.1
unnamed: C15.1, R3.2, XTAL2.2
unnamed: C18.1, DD2.5 (OSCIN/(PD0)), XTAL2.1
unnamed: C2.1, Q1.2 (Vs), Q3.3, R7.2
unnamed: DD2.12 (ADC1-2/T2C3/T15C1/TX2/PA2), R1.1
unnamed: Q2.GA, R4.2
unnamed: DD2.11 (ADC1-1/T2C2/PA1), R6.1
unnamed: DD2.13 (ADC1-3/T2C4/T15C2/RX2/PA3), R4.1
unnamed: Q2.BA, R6.2
unnamed: DA1.1, Q5.1 (B), TP2.1
unnamed: C1.1, DA1.3, R5.2, R10.1
unnamed: DD2.39 (PB3/JTDO/(T2C2)), F1.1
unnamed: DD2.46 (PB9/T4C4/T17C1), F7.1
unnamed: Q4.1 (B), R2.2
unnamed: DD2.45 (PB8/T4C3/T16C1), F6.1
unnamed: DD2.42 (PB6/SCL1/T4C1/T16C1N), F4.1
unnamed: DD2.43 (PB7/SDA1/T4C2/T17C1N), F5.1
unnamed: D1.A, Q2.RA, R1.2
unnamed: Q6.3 (C), R8.1, R14.1
unnamed: Q6.1 (B), R9.2
unnamed: C6.2, DA2.7 (Feedback), R12.2, R13.1
unnamed: DD2.40 (PB4/JTRST/(T3C1)), F2.1
unnamed: DD2.41 (PB5/(T3C2)), F3.1

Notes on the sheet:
UART TX/RX
CPU
Programming
Debug connector
Peripherals usage USB UART1 - output/input TIM1 Ch1 - Xotar LED TIM2 Ch2,3,4 - RGB LED TIM3 Ch1 - Xotar In TIM15 Ch1 - Buzzer TIM ? - Xotar Data timings
Power
3xAAA or 12V
Stabilizer
Address settings

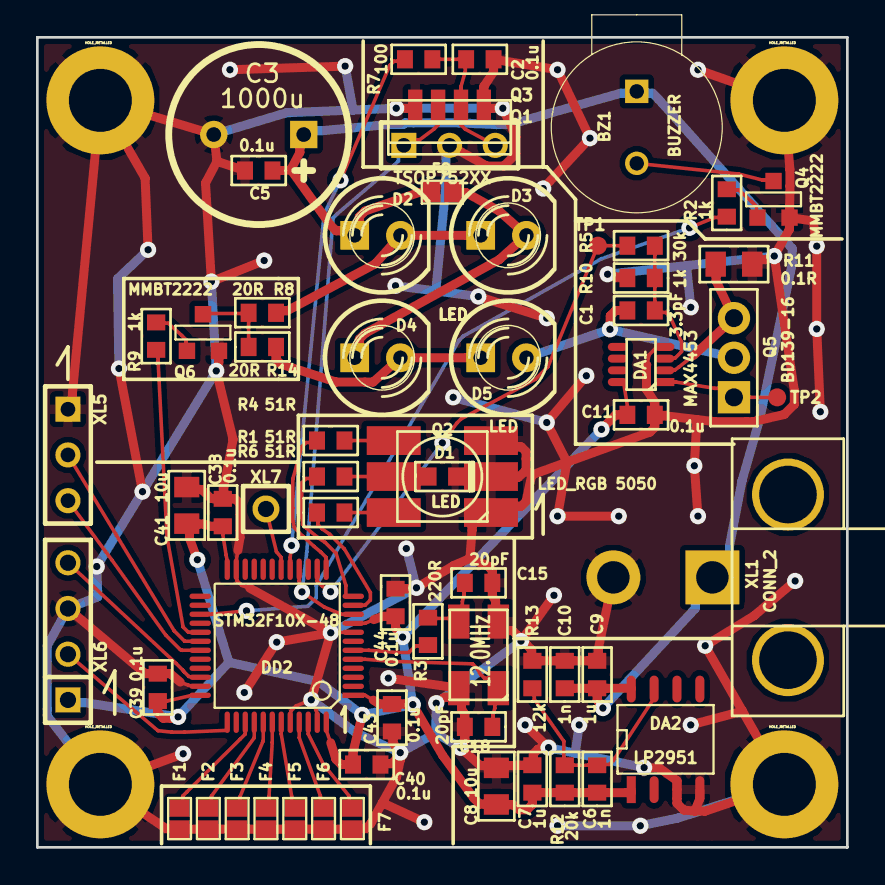
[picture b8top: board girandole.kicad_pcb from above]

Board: 2 copper layers, 45.0 x 45.0 mm, 66 parts (0 on the bottom side), 42 nets.
